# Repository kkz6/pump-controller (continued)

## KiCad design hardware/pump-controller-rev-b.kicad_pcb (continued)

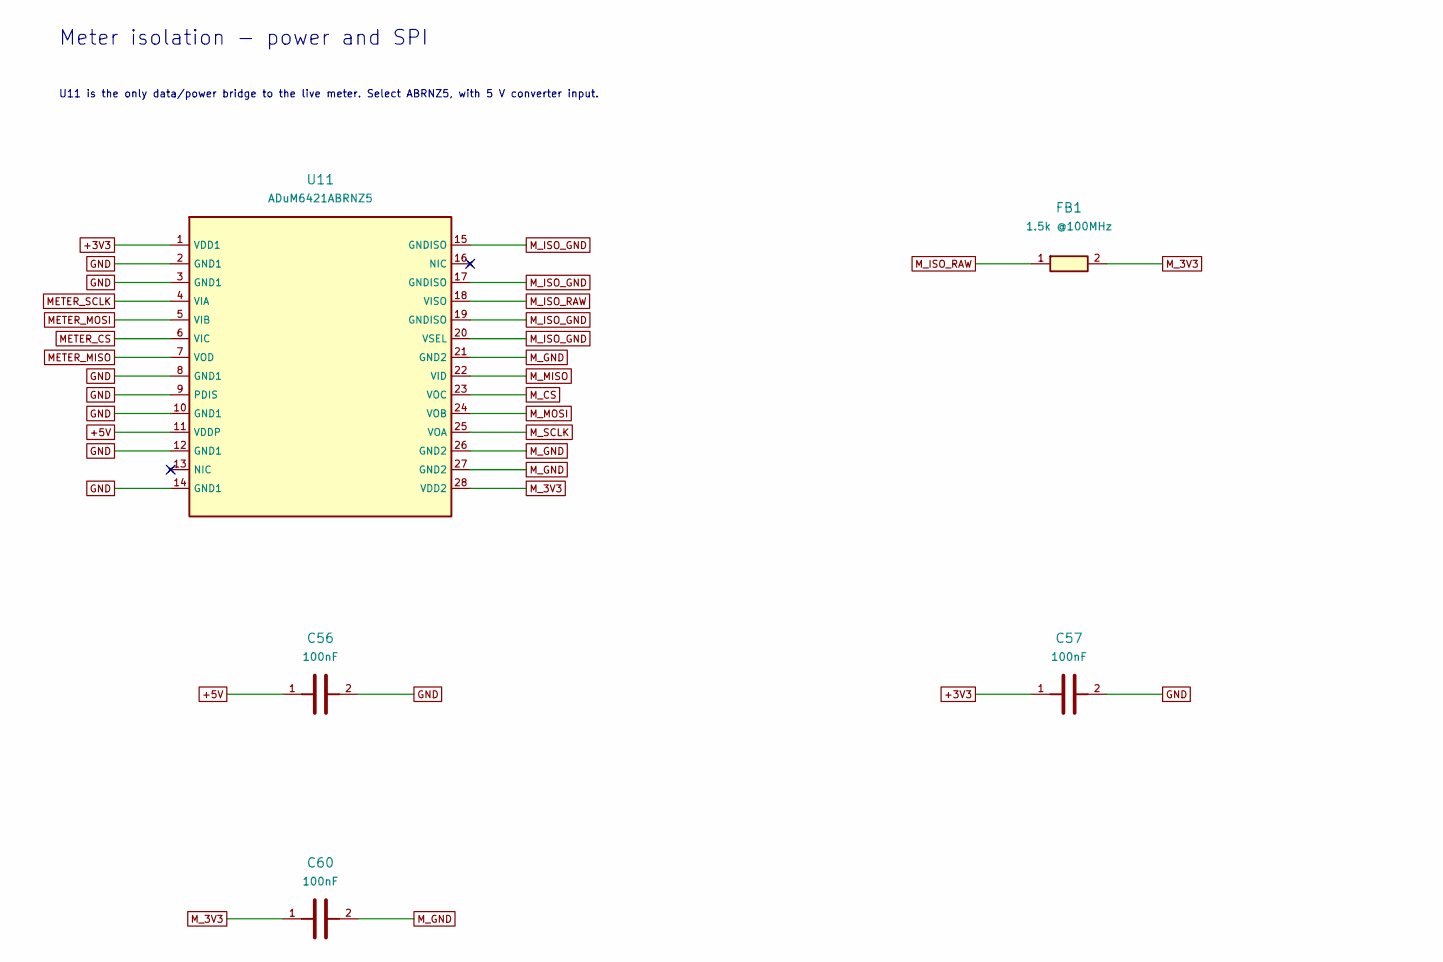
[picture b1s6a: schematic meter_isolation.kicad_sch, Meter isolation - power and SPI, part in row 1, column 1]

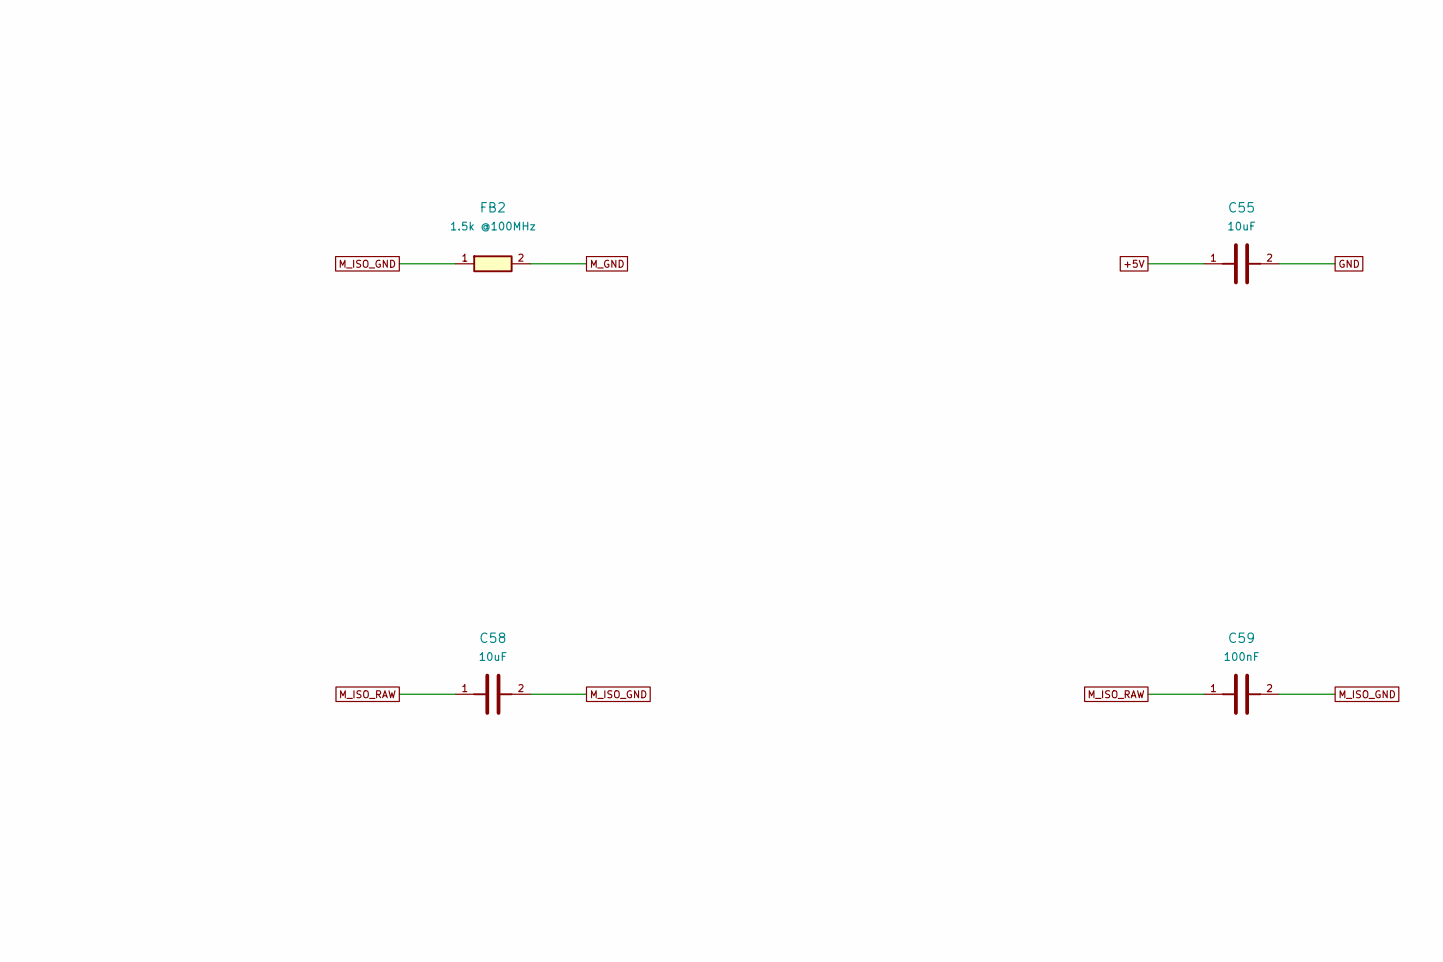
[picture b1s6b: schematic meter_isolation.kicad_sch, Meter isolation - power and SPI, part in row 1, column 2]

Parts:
C55, C58: 10uF; C_0805_2012Metric; MPN SPEC: 10uF X7R, 10%, 16V
C56, C57, C59, C60: 100nF; C_0603_1608Metric; MPN SPEC: 100nF X7R, 10%, 16V
FB1, FB2: 1.5k @100MHz; L_0603_1608Metric; MPN BLM18HE152SN1D
U11: ADuM6421ABRNZ5; ADuM6421A_RN28; MPN ADUM6421ABRNZ5

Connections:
+3V3: C57.1, U11.1 (VDD1); also elsewhere on the board
+5V: C55.1, C56.1, U11.11 (VDDP); also elsewhere on the board
GND: C55.2, C56.2, C57.2, U11.2 (GND1), U11.3 (GND1), U11.8 (GND1), U11.9 (PDIS), U11.10 (GND1), U11.12 (GND1), U11.14 (GND1); also elsewhere on the board
METER_CS: U11.6 (VIC); also elsewhere on the board
METER_MISO: U11.7 (VOD); also elsewhere on the board
METER_MOSI: U11.5 (VIB); also elsewhere on the board
METER_SCLK: U11.4 (VIA); also elsewhere on the board
M_3V3: C60.1, FB1.2, U11.28 (VDD2); also elsewhere on the board
M_CS: U11.23 (VOC); also elsewhere on the board
M_GND: C60.2, FB2.2, U11.21 (GND2), U11.26 (GND2), U11.27 (GND2); also elsewhere on the board
M_ISO_GND: C58.2, C59.2, FB2.1, U11.15 (GNDISO), U11.17 (GNDISO), U11.19 (GNDISO), U11.20 (VSEL)
M_ISO_RAW: C58.1, C59.1, FB1.1, U11.18 (VISO)
M_MISO: U11.22 (VID); also elsewhere on the board
M_MOSI: U11.24 (VOB); also elsewhere on the board
M_SCLK: U11.25 (VOA); also elsewhere on the board

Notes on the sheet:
Meter isolation - power and SPI
U11 is the only data/power bridge to the live meter. Select ABRNZ5, with 5 V converter input.

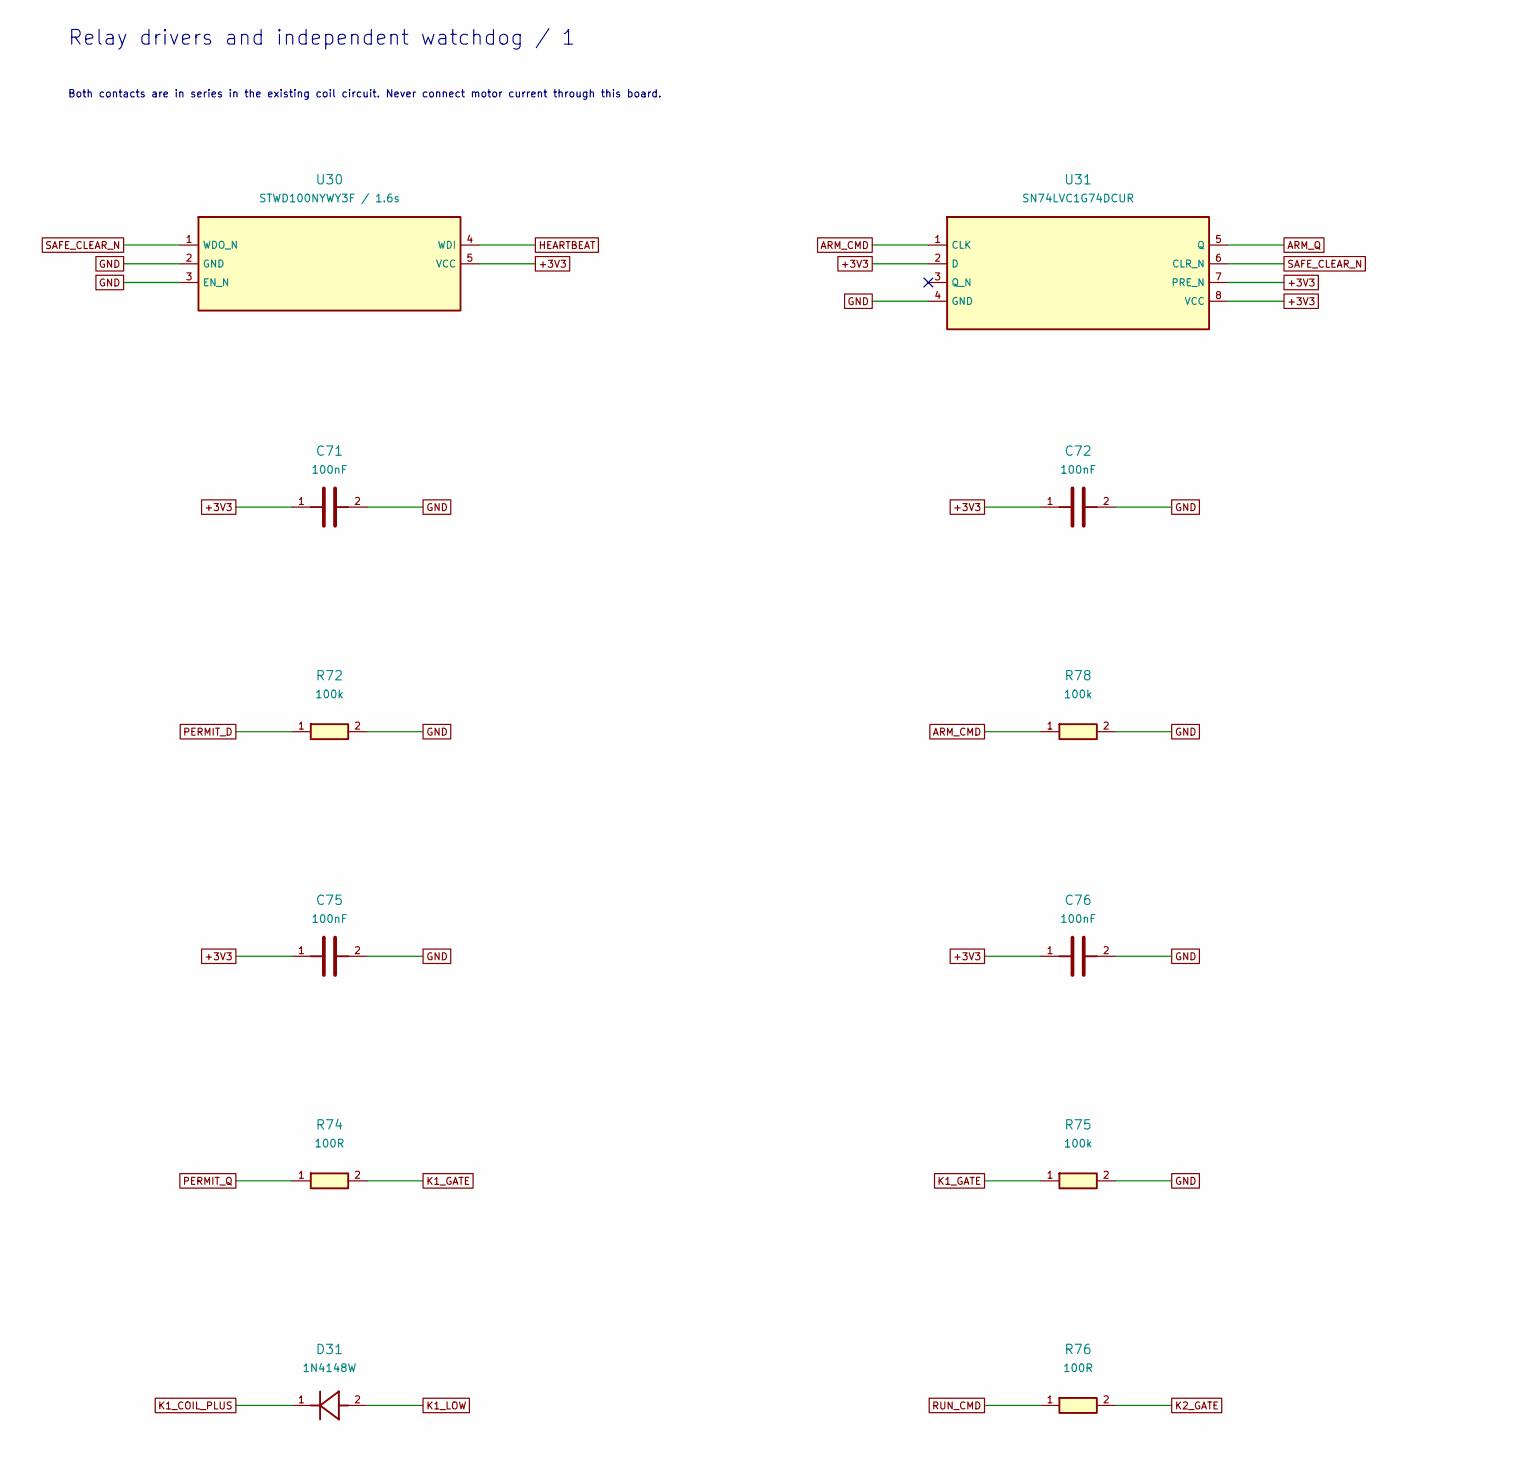
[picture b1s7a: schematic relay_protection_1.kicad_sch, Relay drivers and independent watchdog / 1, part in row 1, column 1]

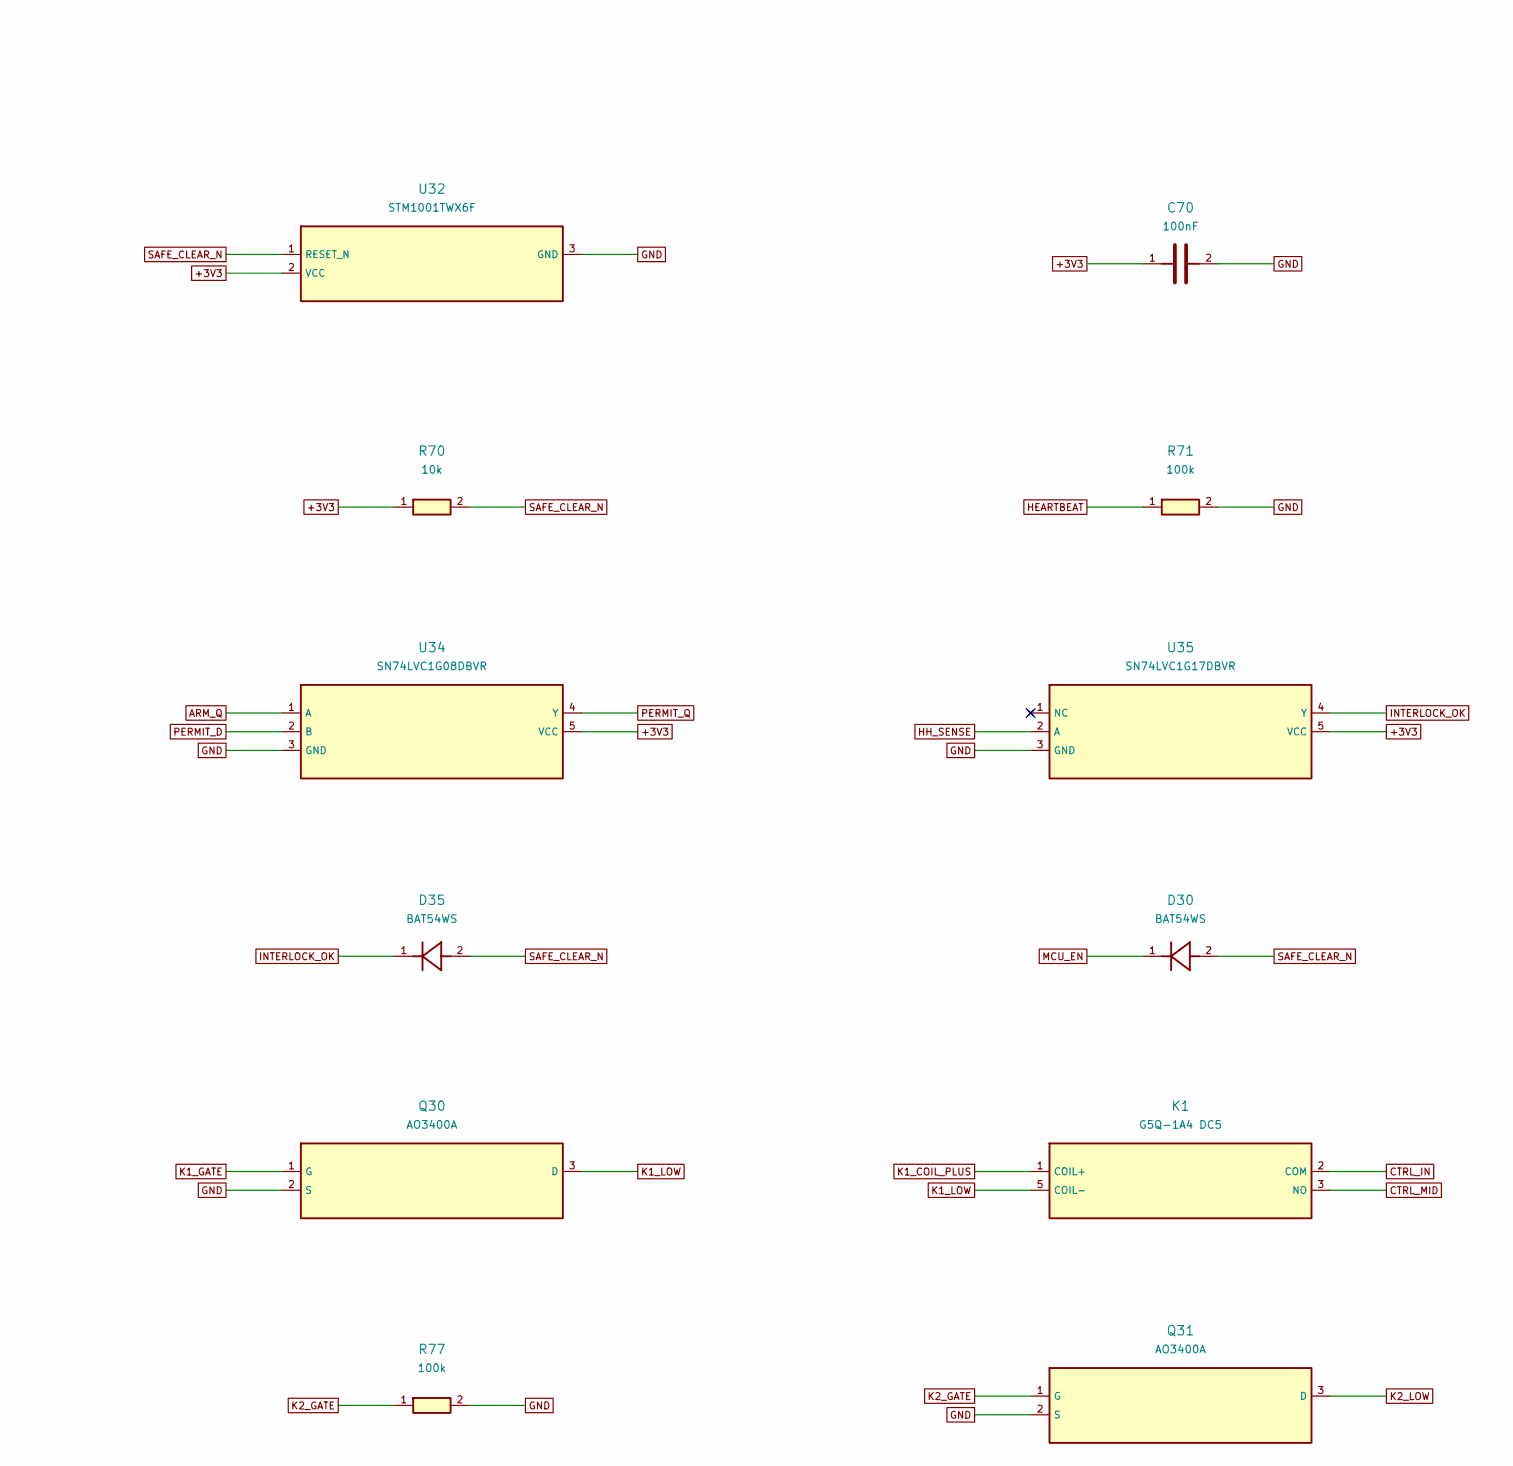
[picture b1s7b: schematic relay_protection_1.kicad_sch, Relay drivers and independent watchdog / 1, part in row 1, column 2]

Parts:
C70, C71, C72, C75, C76: 100nF; C_0603_1608Metric; MPN SPEC: 100nF X7R, 10%, 16V
D30, D35: BAT54WS; D_SOD-323; MPN BAT54WS-7-F
D31: 1N4148W; D_SOD-123; MPN 1N4148W-7-F
K1: G5Q-1A4 DC5; Relay_G5Q_8mm; MPN G5Q-1A4 DC5
Q30, Q31: AO3400A; SOT-23; MPN AO3400A
R70: 10k; R_0603_1608Metric; MPN SPEC: 10k 1%, 0.1W, 0603
R71, R72, R75, R77, R78: 100k; R_0603_1608Metric; MPN SPEC: 100k 1%, 0.1W, 0603
R74, R76: 100R; R_0603_1608Metric; MPN SPEC: 100R 1%, 0.1W, 0603
U30: STWD100NYWY3F / 1.6s; SOT-23-5; MPN STWD100NYWY3F
U31: SN74LVC1G74DCUR; VSSOP-8_2.3x2mm_P0.5mm; MPN SN74LVC1G74DCUR
U32: STM1001TWX6F; SOT-23; MPN STM1001TWX6F
U34: SN74LVC1G08DBVR; SOT-23-5; MPN SN74LVC1G08DBVR
U35: SN74LVC1G17DBVR; SOT-23-5; MPN SN74LVC1G17DBVR

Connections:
+3V3: C70.1, C71.1, C72.1, C75.1, C76.1, R70.1, U30.5 (VCC), U31.2 (D), U31.7 (PRE_N), U31.8 (VCC), U32.2 (VCC), U34.5 (VCC), U35.5 (VCC); also elsewhere on the board
ARM_CMD: R78.1, U31.1 (CLK); also elsewhere on the board
ARM_Q: U31.5 (Q), U34.1 (A)
CTRL_IN: K1.2 (COM); also elsewhere on the board
CTRL_MID: K1.3 (NO); also elsewhere on the board
GND: C70.2, C71.2, C72.2, C75.2, C76.2, Q30.2 (S), Q31.2 (S), R71.2, R72.2, R75.2, R77.2, R78.2, U30.2 (GND), U30.3 (EN_N), U31.4 (GND), U32.3 (GND), U34.3 (GND), U35.3 (GND); also elsewhere on the board
HEARTBEAT: R71.1, U30.4 (WDI); also elsewhere on the board
HH_SENSE: U35.2 (A); also elsewhere on the board
INTERLOCK_OK: D35.1, U35.4 (Y); also elsewhere on the board
K1_COIL_PLUS: D31.1, K1.1 (COIL+); also elsewhere on the board
K1_GATE: Q30.1 (G), R74.2, R75.1
K1_LOW: D31.2, K1.5 (COIL-), Q30.3 (D)
K2_GATE: Q31.1 (G), R76.2, R77.1
K2_LOW: Q31.3 (D); also elsewhere on the board
MCU_EN: D30.1; also elsewhere on the board
PERMIT_D: R72.1, U34.2 (B); also elsewhere on the board
PERMIT_Q: R74.1, U34.4 (Y)
RUN_CMD: R76.1; also elsewhere on the board
SAFE_CLEAR_N: D30.2, D35.2, R70.2, U30.1 (WDO_N), U31.6 (CLR_N), U32.1 (RESET_N)

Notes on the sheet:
Relay drivers and independent watchdog / 1
Both contacts are in series in the existing coil circuit. Never connect motor current through this board.

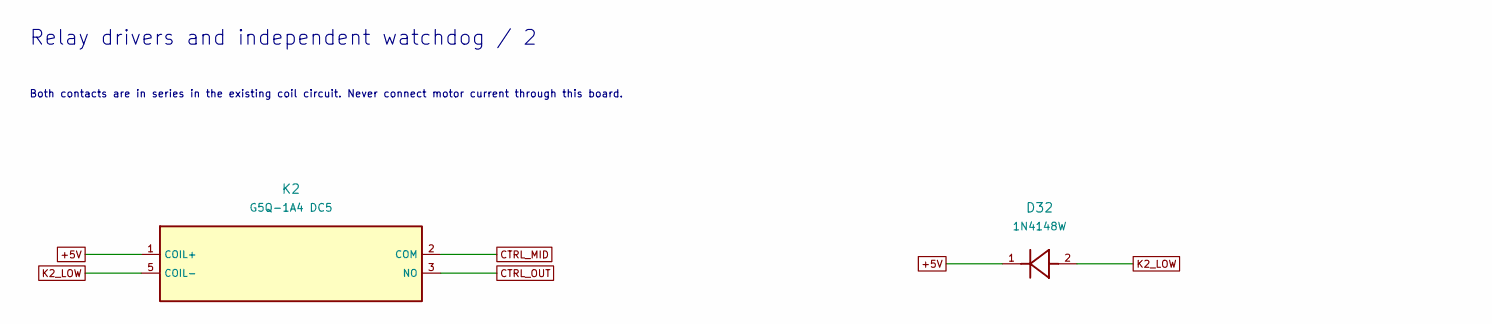
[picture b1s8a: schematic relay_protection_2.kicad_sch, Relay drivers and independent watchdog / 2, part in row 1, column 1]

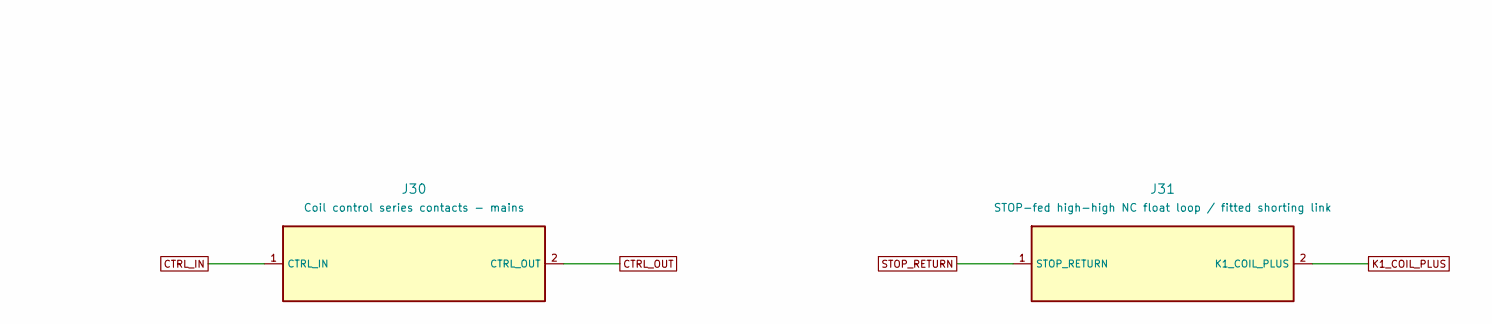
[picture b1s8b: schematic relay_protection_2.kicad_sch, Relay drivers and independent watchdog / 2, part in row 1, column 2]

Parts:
D32: 1N4148W; D_SOD-123; MPN 1N4148W-7-F
J30: Coil control series contacts - mains; PhoenixContact_MC_1,5_2-G-5.08_1x02_P5.08mm_Horizontal; MPN 1836189
J31: STOP-fed high-high NC float loop / fitted shortin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; PhoenixContact_MC_1,5_2-G-3.81_1x02_P3.81mm_Horizontal; MPN Phoenix MC 1,5/2-G-3,81
K2: G5Q-1A4 DC5; Relay_G5Q_8mm; MPN G5Q-1A4 DC5

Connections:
+5V: D32.1, K2.1 (COIL+); also elsewhere on the board
CTRL_IN: J30.1 (CTRL_IN); also elsewhere on the board
CTRL_MID: K2.2 (COM); also elsewhere on the board
CTRL_OUT: J30.2 (CTRL_OUT), K2.3 (NO)
K1_COIL_PLUS: J31.2 (K1_COIL_PLUS); also elsewhere on the board
K2_LOW: D32.2, K2.5 (COIL-); also elsewhere on the board
STOP_RETURN: J31.1 (STOP_RETURN); also elsewhere on the board

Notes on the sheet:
Relay drivers and independent watchdog / 2
Both contacts are in series in the existing coil circuit. Never connect motor current through this board.

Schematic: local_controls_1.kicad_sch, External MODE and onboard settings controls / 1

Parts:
C73, C88, C90: 100nF; C_0603_1608Metric; MPN SPEC: 100nF X7R, 10%, 16V
C74: 1uF; C_0603_1608Metric; MPN SPEC: 1uF X7R, 10%, 16V
C80, C82, C84, C86: 10nF; C_0603_1608Metric; MPN SPEC: 10nF X7R, 10%, 16V
J32: External STOP / START / MODE; pins4,6 reserved; PhoenixContact_MC_1,5_7-G-3.81_1x07_P3.81mm_Horizontal; MPN Phoenix MC 1,5/7-G-3,81
R80, R82, R84, R86: 22k; R_0603_1608Metric; MPN SPEC: 22k 1%, 0.1W, 0603
R81, R83, R85: 33k; R_0603_1608Metric; MPN SPEC: 33k 1%, 0.1W, 0603
R87, R92, R93: 100k; R_0603_1608Metric; MPN SPEC: 100k 1%, 0.1W, 0603
R88, R90: 1k; R_0603_1608Metric; MPN SPEC: 1k 1%, 0.1W, 0603
R89, R91: 10k; R_0603_1608Metric; MPN SPEC: 10k 1%, 0.1W, 0603
U33: MCP23017-E/SS; SSOP-28_5.3x10.2mm_P0.65mm; MPN MCP23017-E/SS

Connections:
+3V3: C73.1, C74.1, R89.1, R91.1, U33.9 (VDD); also elsewhere on the board
+5V: J32.1 (STOP_NC_SUPPLY); also elsewhere on the board
AUTO_RETURN: J32.4 (RESERVED_NEXT), R84.1; also elsewhere on the board
AUTO_SENSE: C84.1, R84.2, R85.1, U33.5 (GPB4)
GND: C73.2, C74.2, C80.2, C82.2, C84.2, C86.2, C88.2, C90.2, J32.7 (BUTTON_GND), R81.2, R83.2, R85.2, R87.2, R92.2, R93.2, U33.10 (VSS), U33.15 (A0), U33.16 (A1), U33.17 (A2); also elsewhere on the board
HH_SENSE: C86.1, R86.2, R87.1; also elsewhere on the board
I2C_SCL: U33.12 (SCL); also elsewhere on the board
I2C_SDA: U33.13 (SDA); also elsewhere on the board
INTERLOCK_OK: U33.6 (GPB5); also elsewhere on the board
K1_COIL_PLUS: R86.1; also elsewhere on the board
MAN_RETURN: J32.3 (MODE_NO_RETURN), R82.1
MAN_SENSE: C82.1, R82.2, R83.1, U33.4 (GPB3)
MCU_EN: U33.18 (RESET_N); also elsewhere on the board
RESET_FILTER: C90.1, R90.2, R91.2, U33.2 (GPB1)
RESET_N: J32.6 (RESERVED_SET), R90.1; also elsewhere on the board
SPARE_B6: R92.1, U33.7 (GPB6); also elsewhere on the board
SPARE_B7: R93.1, U33.8 (GPB7); also elsewhere on the board
START_FILTER: C88.1, R88.2, R89.2, U33.1 (GPB0)
START_N: J32.5 (START_NO), R88.1
STOP_RETURN: J32.2 (STOP_NC_RETURN), R80.1; also elsewhere on the board
STOP_SENSE: C80.1, R80.2, R81.1, U33.3 (GPB2)

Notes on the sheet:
External MODE and onboard settings controls / 1
Rev C: existing START/STOP actuators plus one external MODE button. SW3 SET and SW4 NEXT are on the PCB. STOP/HH clear ARM; mode/settings require STOP event, release and unarmed state.

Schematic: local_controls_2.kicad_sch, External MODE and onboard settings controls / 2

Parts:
J33: OLED I2C 3V3; JST_GH_BM04B-GHS-TBT_1x04-1MP_P1.25mm_Vertical; MPN BM04B-GHS-TBT(LF)(SN)
J34: EXPANSION 3V3 I2C + 2 GPIO; PinHeader_2x03_P1.27mm_Vertical_SMD; MPN SPEC: 2x3 1.27mm vertical SMD header; m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
OLED1: 0.91 inch OLED 128x32 SSD1306; MPN Waveshare 14657 / 0.91inch OLED Module
SW3: SET / RESET; SW_SPST_B3U-1000P; MPN B3U-1000P
SW4: NEXT / +; SW_SPST_B3U-1000P; MPN B3U-1000P

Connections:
+3V3: J33.1 (3V3_100mA), J34.1 (3V3_25mA), OLED1.4 (VCC); also elsewhere on the board
AUTO_RETURN: SW4.1; also elsewhere on the board
GND: J33.2 (GND), J33.MP (Mount), J34.2 (GND), OLED1.3 (GND), SW3.2; also elsewhere on the board
I2C_SCL: J33.4 (SCL), J34.4 (SCL), OLED1.1 (SCL); also elsewhere on the board
I2C_SDA: J33.3 (SDA), J34.3 (SDA), OLED1.2 (SDA); also elsewhere on the board
RESET_N: SW3.1; also elsewhere on the board
SPARE_B6: J34.5 (EXT_IO1); also elsewhere on the board
SPARE_B7: J34.6 (EXT_IO2); also elsewhere on the board
STOP_RETURN: SW4.2; also elsewhere on the board

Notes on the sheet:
External MODE and onboard settings controls / 2
Rev C: existing START/STOP actuators plus one external MODE button. SW3 SET and SW4 NEXT are on the PCB. STOP/HH clear ARM; mode/settings require STOP event, release and unarmed state.

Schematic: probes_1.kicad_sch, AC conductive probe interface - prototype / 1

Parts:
C100: 100nF; C_0603_1608Metric; MPN SPEC: 100nF X7R 16V 10%
C101: 1uF; C_0603_1608Metric; MPN SPEC: 1uF X7R 16V 10%
C110, C111, C112, C113: 10nF; C_0603_1608Metric; MPN SPEC: 10nF X7R 16V 10%
R100, R101: 10k; R_0603_1608Metric; MPN SPEC: 10k 0.1%, >=0.1 W 0603
R102: 47; R_0603_1608Metric; MPN SPEC: 47 1%, >=0.1 W 0603
R103: 27k; R_0603_1608Metric; MPN SPEC: 27k 1%, >=0.1 W 0603
R104: 43k; R_0603_1608Metric; MPN SPEC: 43k 1%, >=0.1 W 0603
R105, R106, R107, R108: 100k; R_0603_1608Metric; MPN SPEC: 100k 1%, >=0.1 W 0603
R109: 10k; R_0603_1608Metric; MPN SPEC: 10k 1%, >=0.1 W 0603
R110, R111, R112, R113: 100; R_0603_1608Metric; MPN SPEC: 100 1%, >=0.1 W 0603
R114: 1M; R_0603_1608Metric; MPN SPEC: 1M 1%, >=0.1 W 0603
U20: TLV9004; TSSOP-14_4.4x5mm_P0.65mm; MPN TLV9004IPWR
U21: TMUX1208; TSSOP-16_4.4x5mm_P0.65mm; MPN TMUX1208PWR
U22: ADS1115; TSSOP-10_3x3mm_P0.5mm; MPN ADS1115IDGSR

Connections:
+3V3: R100.1, R109.2, U20.4 (V+), U21.2 (EN), U21.13 (VDD), U22.8 (VDD); also elsewhere on the board
GND: C100.2, C101.2, C110.2, C111.2, C112.2, C113.2, R101.2, R105.2, R106.2, R107.2, R108.2, U20.11 (V-), U21.14 (GND), U22.1 (ADDR), U22.3 (GND); also elsewhere on the board
I2C_SCL: U22.10 (SCL); also elsewhere on the board
I2C_SDA: U22.9 (SDA); also elsewhere on the board
MUX_A0: R106.1, U21.1 (A0); also elsewhere on the board
MUX_A1: R107.1, U21.16 (A1); also elsewhere on the board
MUX_A2: R108.1, U21.15 (A2); also elsewhere on the board
PROBE_ADC_BIAS: C111.1, R111.2, U22.5 (AIN1)
PROBE_ADC_BIAS2: C113.1, R113.2, U22.7 (AIN3)
PROBE_ADC_RDY: R109.1, U22.2 (ALERT_RDY)
PROBE_ADC_SIGNAL: C110.1, R110.2, U22.4 (AIN0)
PROBE_ADC_TX: C112.1, R112.2, U22.6 (AIN2)
PROBE_BIAS: C101.1, R102.2, R104.1, R111.1, R113.1, R114.2, U21.11 (S6); also elsewhere on the board
PROBE_BIAS_DIV: C100.1, R100.2, R101.1, U20.3 (IN1+)
PROBE_BIAS_RAW: R102.1, U20.1 (OUT1), U20.2 (IN1-)
PROBE_EXC: R103.1, R105.1; also elsewhere on the board
PROBE_INLET_ADC: U21.12 (S5); also elsewhere on the board
PROBE_L1_ADC: U21.4 (S1); also elsewhere on the board
PROBE_L2_ADC: U21.5 (S2); also elsewhere on the board
PROBE_L3_ADC: U21.6 (S3); also elsewhere on the board
PROBE_L4_ADC: U21.7 (S4); also elsewhere on the board
PROBE_MUX_BUF: R110.1, U20.8 (OUT3), U20.9 (IN3-)
PROBE_MUX_OUT: R114.1, U20.10 (IN3+), U21.8 (D)
PROBE_TX_INLET: U20.13 (IN4-), U20.14 (OUT4), U21.9 (S8); also elsewhere on the board
PROBE_TX_SET: R103.2, R104.2, U20.5 (IN2+), U20.12 (IN4+)
PROBE_TX_TANK: R112.1, U20.6 (IN2-), U20.7 (OUT2), U21.10 (S7); also elsewhere on the board

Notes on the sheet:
AC conductive probe interface - prototype / 1

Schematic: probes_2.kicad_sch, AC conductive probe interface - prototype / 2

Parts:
C102, C103, C104: 100nF; C_0603_1608Metric; MPN SPEC: 100nF X7R 16V 10%
C105: 4.7uF; C_0603_1608Metric; MPN SPEC: 4.7uF X7R 16V 10%
C106, C107, C108, C109, C120: 1uF; C_0805_2012Metric; MPN C2012X7R1H105K125AB
D100, D101, D110: PESD5V0S1BA; D_SOD-323; MPN PESD5V0S1BA,115
D102, D103: BAT54S; SOT-23; MPN BAT54S,215
R115, R118: 2.2k; R_0603_1608Metric; MPN SPEC: 2.2k 1%, >=0.1 W 0603
R116, R117, R119, R120: 4.99k; R_1206_3216Metric; MPN CRCW12064K99FKEA
R130, R131: 10k; R_1206_3216Metric; MPN CRCW120610K0FKEA
R132: 47k; R_0603_1608Metric; MPN SPEC: 47k 1%, >=0.1 W 0603
R133: 22k; R_0603_1608Metric; MPN SPEC: 22k 1%, >=0.1 W 0603

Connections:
+3V3: C102.1, C103.1, C104.1, C105.1, D102.2 (K2), D103.2 (K2); also elsewhere on the board
GND: C102.2, C103.2, C104.2, C105.2, D100.2, D101.2, D102.1 (A1), D103.1 (A1), D110.2; also elsewhere on the board
PROBE_BIAS: R132.2; also elsewhere on the board
PROBE_ICOM: R120.2; also elsewhere on the board
PROBE_ICOM_CLAMP: C107.2, C109.2, D101.1, R119.1
PROBE_ICOM_DRIVE: C107.1, C109.1, D103.3 (K1_A2), R118.2
PROBE_ICOM_MID: R119.2, R120.1
PROBE_L1: R130.1; also elsewhere on the board
PROBE_L1_ADC: R133.2; also elsewhere on the board
PROBE_L1_CLAMP: C120.1, D110.1, R131.2
PROBE_L1_MID: R130.2, R131.1
PROBE_L1_SENSE: C120.2, R132.1, R133.1
PROBE_TCOM: R117.2; also elsewhere on the board
PROBE_TCOM_CLAMP: C106.2, C108.2, D100.1, R116.1
PROBE_TCOM_DRIVE: C106.1, C108.1, D102.3 (K1_A2), R115.2
PROBE_TCOM_MID: R116.2, R117.1
PROBE_TX_INLET: R118.1; also elsewhere on the board
PROBE_TX_TANK: R115.1; also elsewhere on the board

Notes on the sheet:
AC conductive probe interface - prototype / 2

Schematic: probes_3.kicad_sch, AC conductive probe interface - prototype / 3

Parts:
C121, C123, C125: 1nF; C_0603_1608Metric; MPN SPEC: 1nF C0G 50V 5%
C122, C124, C126: 1uF; C_0805_2012Metric; MPN C2012X7R1H105K125AB
D111, D113, D115: BAS70-04; SOT-23; MPN BAS70-04,215
D112, D114, D116: PESD5V0S1BA; D_SOD-323; MPN PESD5V0S1BA,115
R140, R141, R150, R151, R160, R161: 10k; R_1206_3216Metric; MPN CRCW120610K0FKEA
R142, R152, R162: 47k; R_0603_1608Metric; MPN SPEC: 47k 1%, >=0.1 W 0603
R143, R153, R163: 22k; R_0603_1608Metric; MPN SPEC: 22k 1%, >=0.1 W 0603

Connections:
+3V3: D111.2 (K2), D113.2 (K2), D115.2 (K2); also elsewhere on the board
GND: D111.1 (A1), D112.2, D113.1 (A1), D114.2, D115.1 (A1), D116.2; also elsewhere on the board
PROBE_BIAS: C121.2, C123.2, C125.2, R142.2, R152.2, R162.2; also elsewhere on the board
PROBE_L1_ADC: C121.1, D111.3 (K1_A2); also elsewhere on the board
PROBE_L2: R140.1; also elsewhere on the board
PROBE_L2_ADC: C123.1, D113.3 (K1_A2), R143.2; also elsewhere on the board
PROBE_L2_CLAMP: C122.1, D112.1, R141.2
PROBE_L2_MID: R140.2, R141.1
PROBE_L2_SENSE: C122.2, R142.1, R143.1
PROBE_L3: R150.1; also elsewhere on the board
PROBE_L3_ADC: C125.1, D115.3 (K1_A2), R153.2; also elsewhere on the board
PROBE_L3_CLAMP: C124.1, D114.1, R151.2
PROBE_L3_MID: R150.2, R151.1
PROBE_L3_SENSE: C124.2, R152.1, R153.1
PROBE_L4: R160.1; also elsewhere on the board
PROBE_L4_ADC: R163.2; also elsewhere on the board
PROBE_L4_CLAMP: C126.1, D116.1, R161.2
PROBE_L4_MID: R160.2, R161.1
PROBE_L4_SENSE: C126.2, R162.1, R163.1

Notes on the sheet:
AC conductive probe interface - prototype / 3

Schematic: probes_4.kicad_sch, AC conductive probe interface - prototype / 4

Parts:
C127, C129: 1nF; C_0603_1608Metric; MPN SPEC: 1nF C0G 50V 5%
C128: 1uF; C_0805_2012Metric; MPN C2012X7R1H105K125AB
D117, D119: BAS70-04; SOT-23; MPN BAS70-04,215
D118: PESD5V0S1BA; D_SOD-323; MPN PESD5V0S1BA,115
J20: TANK PROBES; PhoenixContact_MC_1,5_5-G-3.81_1x05_P3.81mm_Horizontal; MPN 1803303
J21: INLET PROBES; PhoenixContact_MC_1,5_2-G-3.81_1x02_P3.81mm_Horizontal; MPN 1803277
R170, R171: 10k; R_1206_3216Metric; MPN CRCW120610K0FKEA
R172: 47k; R_0603_1608Metric; MPN SPEC: 47k 1%, >=0.1 W 0603
R173: 22k; R_0603_1608Metric; MPN SPEC: 22k 1%, >=0.1 W 0603

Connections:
+3V3: D117.2 (K2), D119.2 (K2); also elsewhere on the board
GND: D117.1 (A1), D118.2, D119.1 (A1); also elsewhere on the board
PROBE_BIAS: C127.2, C129.2, R172.2; also elsewhere on the board
PROBE_ICOM: J21.2 (INLET_COM); also elsewhere on the board
PROBE_INLET: J21.1 (INLET), R170.1
PROBE_INLET_ADC: C129.1, D119.3 (K1_A2), R173.2; also elsewhere on the board
PROBE_INLET_CLAMP: C128.1, D118.1, R171.2
PROBE_INLET_MID: R170.2, R171.1
PROBE_INLET_SENSE: C128.2, R172.1, R173.1
PROBE_L1: J20.2 (L1); also elsewhere on the board
PROBE_L2: J20.3 (L2); also elsewhere on the board
PROBE_L3: J20.4 (L3); also elsewhere on the board
PROBE_L4: J20.5 (L4); also elsewhere on the board
PROBE_L4_ADC: C127.1, D117.3 (K1_A2); also elsewhere on the board
PROBE_TCOM: J20.1 (COM); also elsewhere on the board

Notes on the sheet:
AC conductive probe interface - prototype / 4

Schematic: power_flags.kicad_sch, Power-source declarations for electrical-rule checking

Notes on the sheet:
Power-source declarations for electrical-rule checking
